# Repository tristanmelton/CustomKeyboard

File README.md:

### Custom Keyboard and Numpad - Beryl.
I had some problems with Amethyst, namely:
- USB-Micro instead of USB-C
- Wired takes up an already-limited USB slot
- A little tall to type on
- Non-customizable key switches

So for Beryl, I'm proposing:
- USB-C with the nice!nano microcontroller. Also covers wireless with the built-in bluetooth.
- Going to use Kailh switches with low-profile to shorten the height, with hot-swap sockets.  

### Changelog
## 1/25/2025
I did some initial re-organization and copied the v1 to a v2 folder for initial setup. The MCU was replaced with a nice!nano and I'm using hot-swappable Kailh choc switches now.
Board should be laid out and everything - it's been sent off with JLCPCB.

PURCHASED:
- PCB x5 from JLCPCB
- Battery from Amazon
- Kailh hot-swappable sockets x100 from AliExpress
- nice!nano v2 x5 from AliExpress
- JST Connector from Digikey
- Sliding switch from Digikey
- Kailh Low Profile Choc Switches (red) x80 from Typeractive

I only have not ordered Keycaps yet. If you have any suggestions please let me know.

## 2/11/2025
I have updated the PCB with a silly mistake that had GND and VCC swapped on the battery. The software is complete and can be found (https://github.com/tristanmelton/cheapino-zmk-config-single-nicenano). The direct uf2 is also in the Software folder.

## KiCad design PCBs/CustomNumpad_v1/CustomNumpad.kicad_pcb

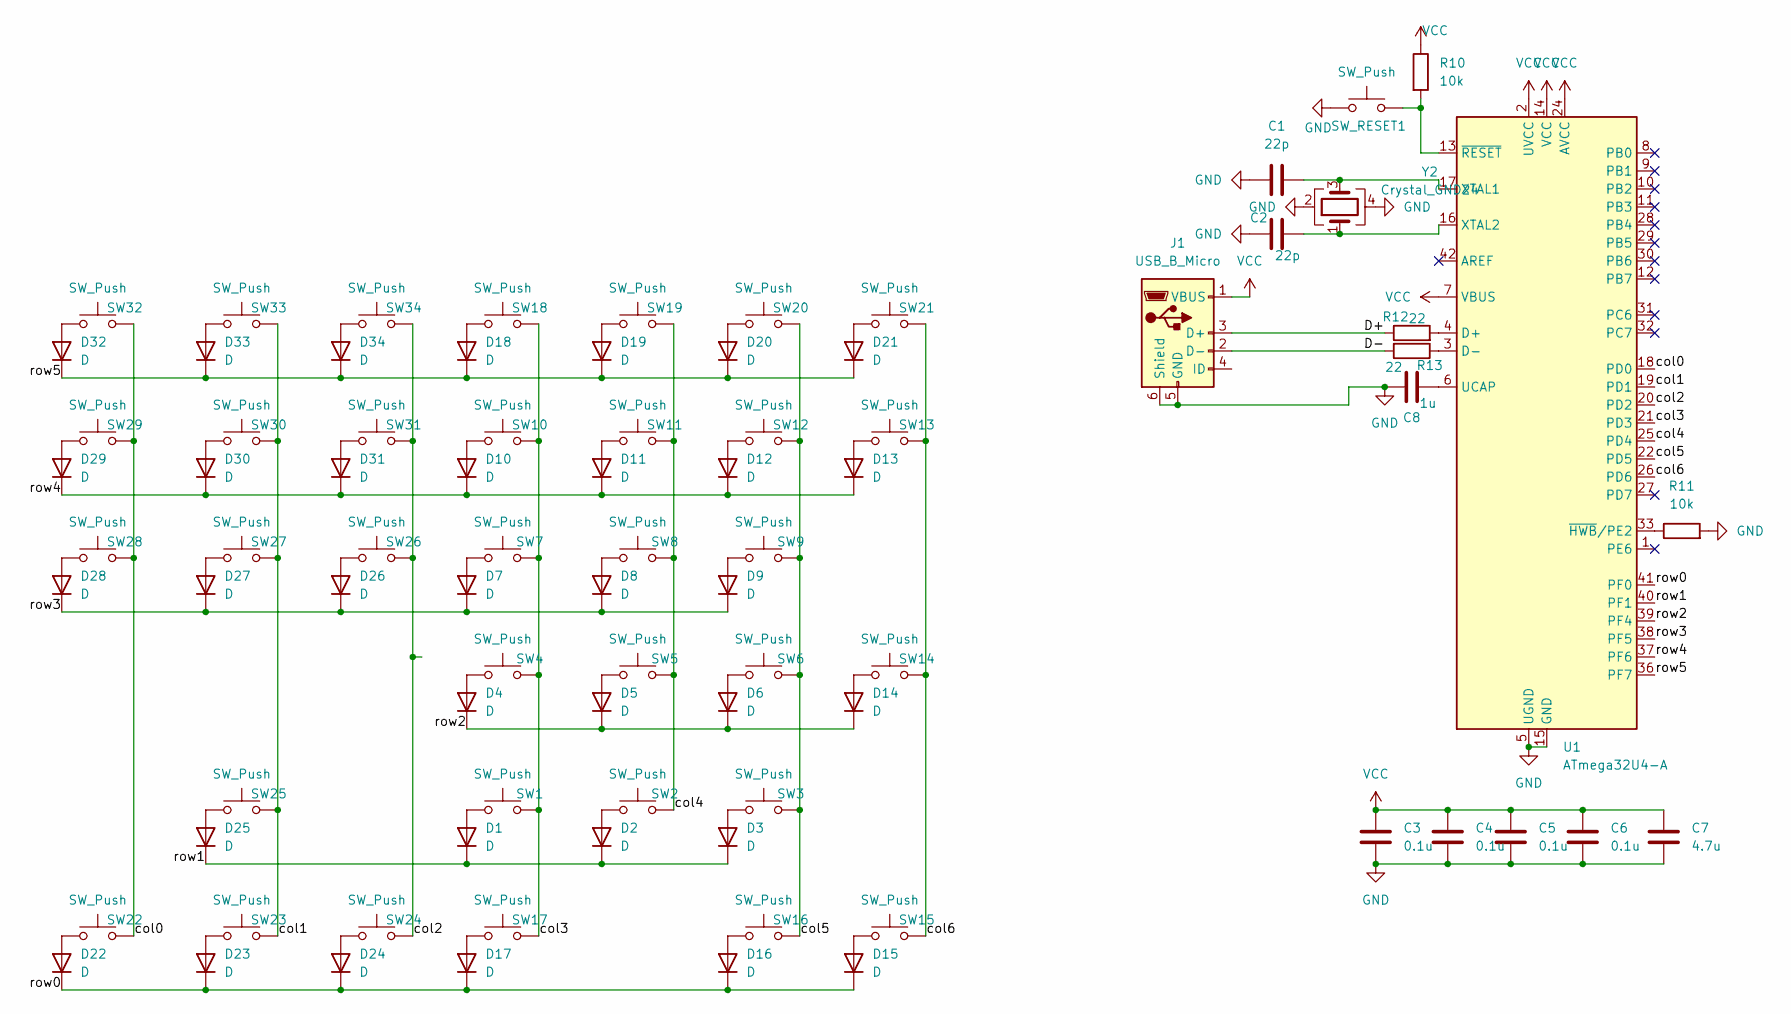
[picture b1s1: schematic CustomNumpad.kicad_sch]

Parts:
C1, C2: 22p; C_0603_1608Metric
C3, C4, C5, C6: 0.1u; C_0603_1608Metric
C7: 4.7u; C_0603_1608Metric
C8: 1u; C_0603_1608Metric
D1, D2, D3, D4, D5, D6, D7, D8, D9, D10, D11, D12, D13, D14, D15, D16, D17, D18, D19, D20, D21, D22, D23, D24, D25, D26, D27, D28, D29, D30, D31, D32, D33, D34: D; D_0603_1608Metric
J1: USB_B_Micro; USB_Micro-B_Amphenol_10118194_Horizontal
R10, R11: 10k; R_0603_1608Metric
R12, R13: 22; R_0603_1608Metric
SW1, SW2, SW3, SW4, SW5, SW6, SW7, SW8, SW9, SW10, SW11, SW12, SW13, SW16, SW18, SW19, SW20, SW21, SW22, SW23, SW24, SW25, SW26, SW27, SW28, SW29, SW30, SW31, SW32, SW33, SW34: SW_Push; SW_Cherry_MX_PCB_1.00u
SW14, SW15: SW_Push; SW_Cherry_MX_PCB_2.00u_90deg
SW17: SW_Push; SW_Cherry_MX_PCB_2.00u
SW_RESET1: SW_Push; SW_SPST_TL3342
U1: ATmega32U4-A; TQFP-44_10x10mm_P0.8mm
Y2: Crystal_GND24; Crystal_SMD_SeikoEpson_FA238-4Pin_3.2x2.5mm

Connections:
/D+: J1.3 (D+), R12.1
/D-: J1.2 (D-), R13.2
/col0: SW22.2, SW28.2, SW29.2, SW32.2, U1.18 (PD0)
/col1: SW23.2, SW25.2, SW27.2, SW30.2, SW33.2, U1.19 (PD1)
/col2: SW24.2, SW26.2, SW31.2, SW34.2, U1.20 (PD2)
/col3: SW1.2, SW4.2, SW7.2, SW10.2, SW17.2, SW18.2, U1.21 (PD3)
/col4: SW2.2, SW5.2, SW8.2, SW11.2, SW19.2, U1.25 (PD4)
/col5: SW3.2, SW6.2, SW9.2, SW12.2, SW16.2, SW20.2, U1.22 (PD5)
/col6: SW13.2, SW14.2, SW15.2, SW21.2, U1.26 (PD6)
/row0: D15.1 (K), D16.1 (K), D17.1 (K), D22.1 (K), D23.1 (K), D24.1 (K), U1.41 (PF0)
/row1: D1.1 (K), D2.1 (K), D3.1 (K), D25.1 (K), U1.40 (PF1)
/row2: D4.1 (K), D5.1 (K), D6.1 (K), D14.1 (K), U1.39 (PF4)
/row3: D7.1 (K), D8.1 (K), D9.1 (K), D26.1 (K), D27.1 (K), D28.1 (K), U1.38 (PF5)
/row4: D10.1 (K), D11.1 (K), D12.1 (K), D13.1 (K), D29.1 (K), D30.1 (K), D31.1 (K), U1.37 (PF6)
/row5: D18.1 (K), D19.1 (K), D20.1 (K), D21.1 (K), D32.1 (K), D33.1 (K), D34.1 (K), U1.36 (PF7)
GND: C1.1, C2.1, C3.2, C4.2, C5.2, C6.2, C7.2, C8.1, J1.5 (GND), J1.6 (Shield), R11.2, SW_RESET1.1, U1.5 (UGND), U1.15 (GND), U1.23 (GND), U1.35 (GND), U1.43 (GND), Y2.2, Y2.4
unnamed: D1.2 (A), SW1.1
unnamed: D2.2 (A), SW2.1
unnamed: D3.2 (A), SW3.1
unnamed: D4.2 (A), SW4.1
unnamed: D5.2 (A), SW5.1
unnamed: D6.2 (A), SW6.1
unnamed: D7.2 (A), SW7.1
unnamed: D8.2 (A), SW8.1
unnamed: D9.2 (A), SW9.1
unnamed: D10.2 (A), SW10.1
unnamed: D11.2 (A), SW11.1
unnamed: D12.2 (A), SW12.1
unnamed: D13.2 (A), SW13.1
unnamed: D14.2 (A), SW14.1
unnamed: D15.2 (A), SW15.1
unnamed: D16.2 (A), SW16.1
unnamed: D17.2 (A), SW17.1
unnamed: D18.2 (A), SW18.1
unnamed: D19.2 (A), SW19.1
unnamed: D20.2 (A), SW20.1
unnamed: D21.2 (A), SW21.1
unnamed: D22.2 (A), SW22.1
unnamed: D23.2 (A), SW23.1
unnamed: D24.2 (A), SW24.1
unnamed: D25.2 (A), SW25.1
unnamed: D26.2 (A), SW26.1
unnamed: D27.2 (A), SW27.1
unnamed: D28.2 (A), SW28.1
unnamed: D29.2 (A), SW29.1
unnamed: D30.2 (A), SW30.1
unnamed: D31.2 (A), SW31.1
unnamed: D32.2 (A), SW32.1
unnamed: D33.2 (A), SW33.1
unnamed: D34.2 (A), SW34.1
unnamed: R12.2, U1.4 (D+)
unnamed: R13.1, U1.3 (D-)
unnamed: C8.2, U1.6 (UCAP)
unnamed: C1.2, U1.17 (XTAL1), Y2.3
unnamed: C2.2, U1.16 (XTAL2), Y2.1
unnamed: R11.1, U1.33 (~HWB/PE2)
unnamed: R10.2, SW_RESET1.2, U1.13 (~RESET)
VCC: C3.1, C4.1, C5.1, C6.1, C7.1, J1.1 (VBUS), R10.1, U1.2 (UVCC), U1.7 (VBUS), U1.14 (VCC), U1.24 (AVCC), U1.34 (VCC), U1.44 (AVCC)

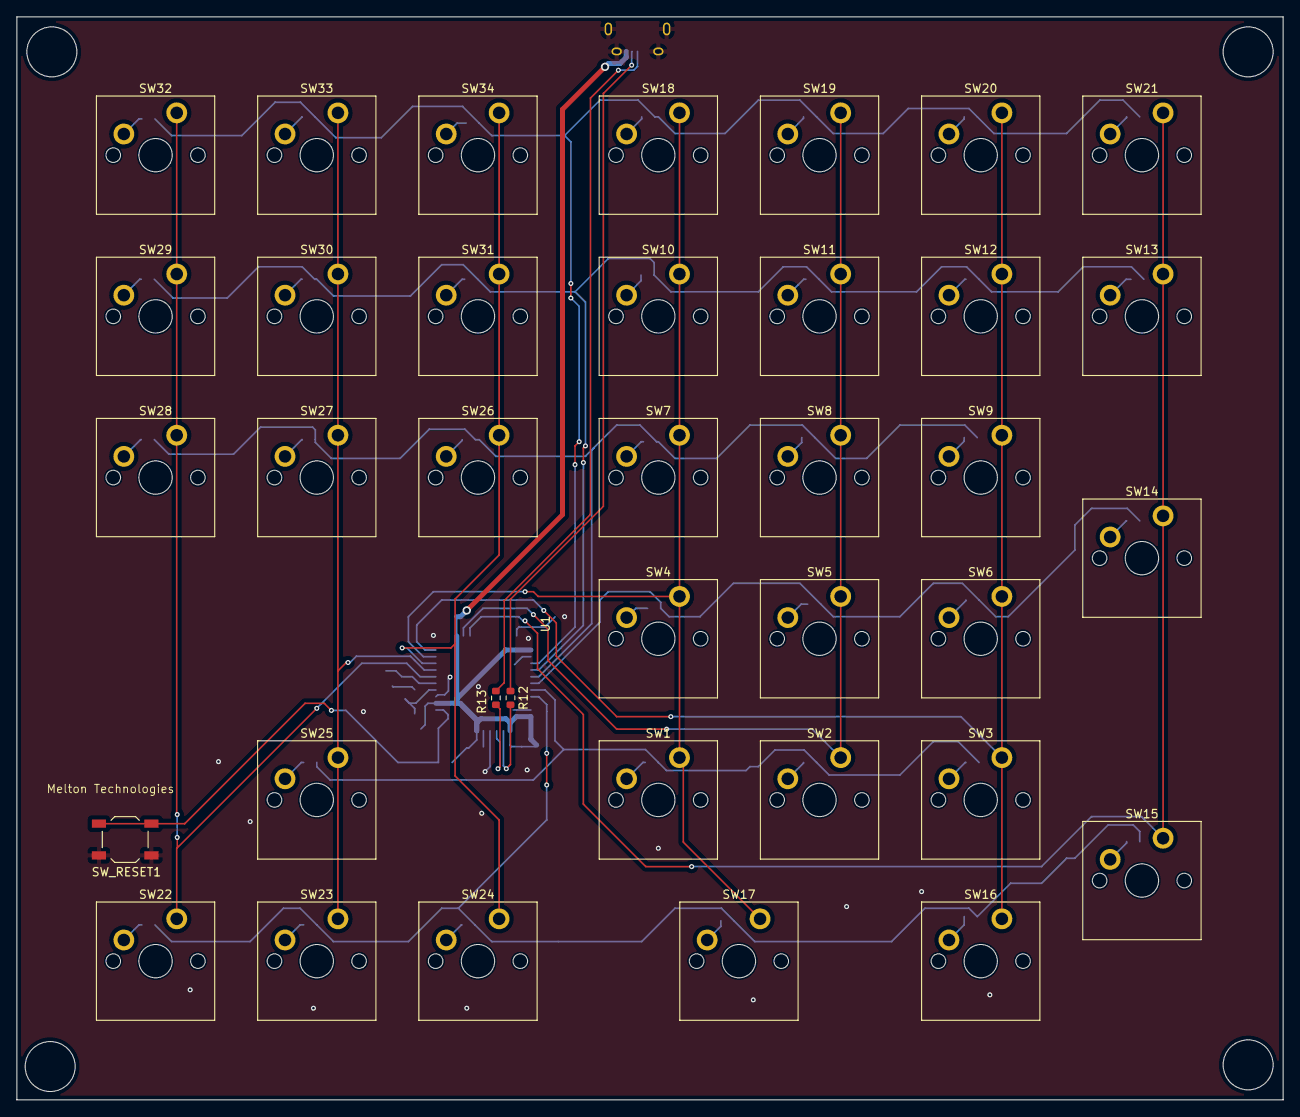
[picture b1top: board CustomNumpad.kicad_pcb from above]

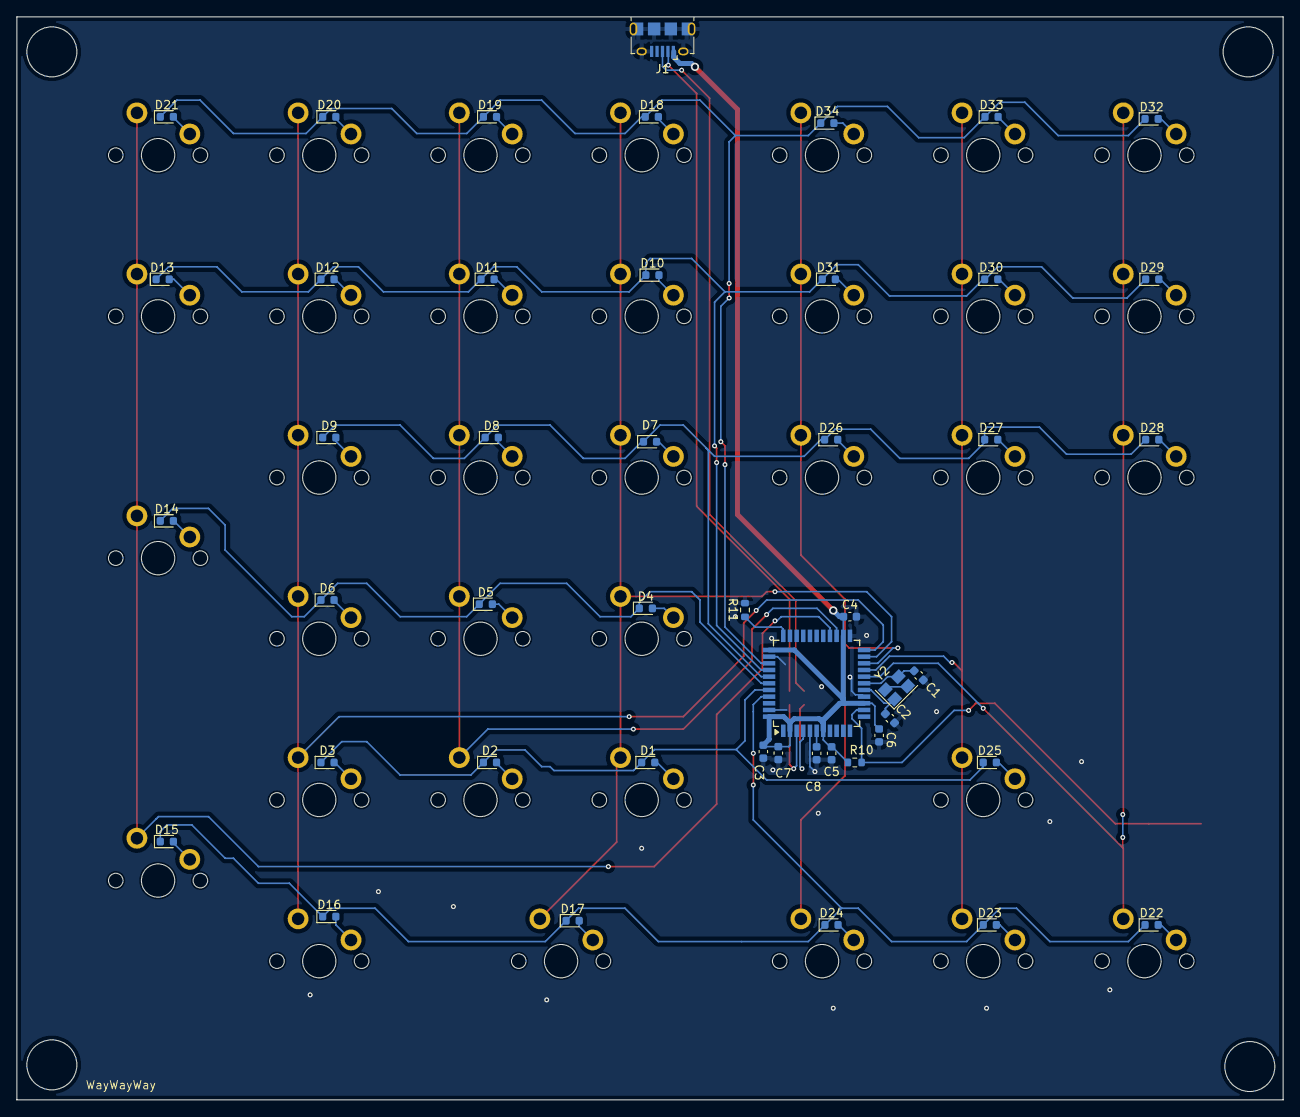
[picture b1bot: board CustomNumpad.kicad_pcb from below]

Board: 2 copper layers, 152.0 x 130.0 mm, 84 parts (47 on the bottom side), 58 nets.

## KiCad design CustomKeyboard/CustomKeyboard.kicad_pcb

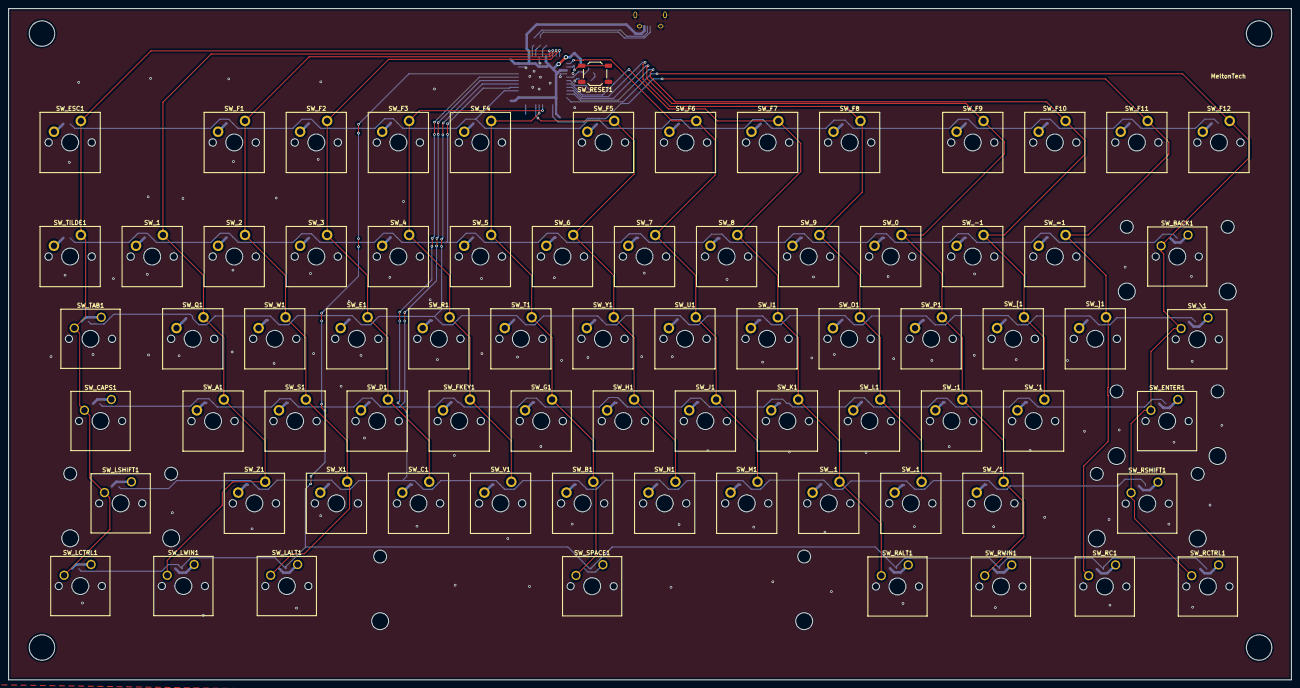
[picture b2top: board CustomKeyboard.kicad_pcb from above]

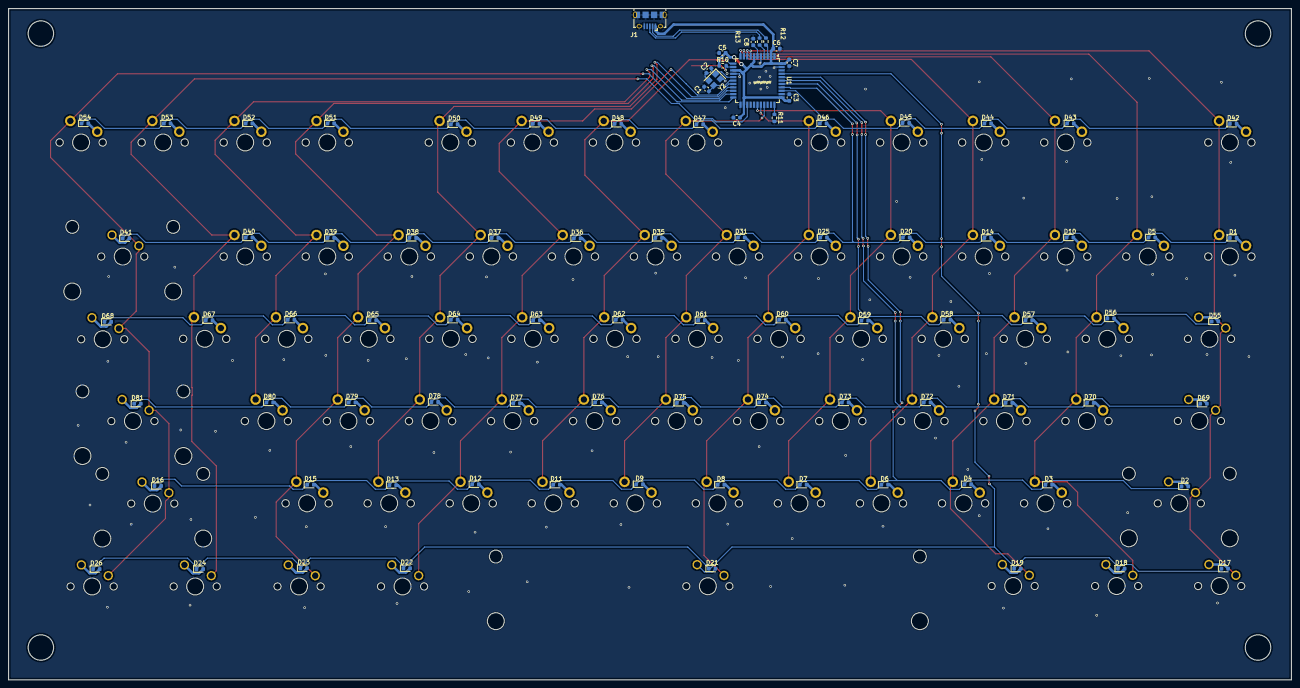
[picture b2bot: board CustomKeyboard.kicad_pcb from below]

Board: 2 copper layers, 302.5 x 158.3 mm, 164 parts (89 on the bottom side), 105 nets.

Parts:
C1, C2: 22p; C_0603_1608Metric
C3, C4, C5, C6: 0.1u; C_0603_1608Metric
C7: 4.7u; C_0603_1608Metric
C8: 1u; C_0603_1608Metric
D1, D2, D3, D4, D5, D6, D7, D8, D9, D10, D11, D12, D13, D14, D15, D16, D17, D18, D19, D20, D21, D22, D23, D24, D25, D26, D31, D35, D36, D37, D38, D39, D40, D41, D42, D43, D44, D45, D46, D47, D48, D49, D50, D51, D52, D53, D54, D55, D56, D57, D58, D59, D60, D61, D62, D63, D64, D65, D66, D67, D68, D69, D70, D71, D72, D73, D74, D75, D76, D77, D78, D79, D80, D81: D; D_0603_1608Metric
J1: USB_B_Micro; USB_Micro-B_Amphenol_10118194_Horizontal
R10, R11: 10k; R_0603_1608Metric
R12, R13: 22; R_0603_1608Metric
SW_0, SW_1, SW_2, SW_3, SW_4, SW_5, SW_6, SW_7, SW_8, SW_9, SW_.1: SW_Push; SW_Cherry_MX_PCB_1.00u
SW_'1: SW_Push; SW_Cherry_MX_PCB_1.00u
SW_,1: SW_Push; SW_Cherry_MX_PCB_1.00u
SW_-1: SW_Push; SW_Cherry_MX_PCB_1.00u
SW_/1: SW_Push; SW_Cherry_MX_PCB_1.00u
SW_;1: SW_Push; SW_Cherry_MX_PCB_1.00u
SW_=1: SW_Push; SW_Cherry_MX_PCB_1.00u
SW_A1: SW_Push; SW_Cherry_MX_PCB_1.00u
SW_B1: SW_Push; SW_Cherry_MX_PCB_1.00u
SW_BACK1: SW_Push; SW_Cherry_MX_2.00u_PCB
SW_C1: SW_Push; SW_Cherry_MX_PCB_1.00u
SW_CAPS1: SW_Push; SW_Cherry_MX_1.75u_PCB
SW_D1: SW_Push; SW_Cherry_MX_PCB_1.00u
SW_E1: SW_Push; SW_Cherry_MX_PCB_1.00u
SW_ENTER1: SW_Push; SW_Cherry_MX_2.25u_PCB
SW_ESC1: SW_Push; SW_Cherry_MX_PCB_1.00u
SW_F1, SW_F2, SW_F3, SW_F4, SW_F5, SW_F6, SW_F7, SW_F8, SW_F9, SW_F10, SW_F11, SW_F12: SW_Push; SW_Cherry_MX_PCB_1.00u
SW_FKEY1: SW_Push; SW_Cherry_MX_PCB_1.00u
SW_G1: SW_Push; SW_Cherry_MX_PCB_1.00u
SW_H1: SW_Push; SW_Cherry_MX_PCB_1.00u
SW_I1: SW_Push; SW_Cherry_MX_PCB_1.00u
SW_J1: SW_Push; SW_Cherry_MX_PCB_1.00u
SW_K1: SW_Push; SW_Cherry_MX_PCB_1.00u
SW_L1: SW_Push; SW_Cherry_MX_PCB_1.00u
SW_LALT1: SW_Push; SW_Cherry_MX_1.25u_PCB
SW_LCTRL1: SW_Push; SW_Cherry_MX_1.25u_PCB
SW_LSHIFT1: SW_Push; SW_Cherry_MX_2.25u_PCB
SW_LWIN1: SW_Push; SW_Cherry_MX_1.25u_PCB
SW_M1: SW_Push; SW_Cherry_MX_PCB_1.00u
SW_N1: SW_Push; SW_Cherry_MX_PCB_1.00u
SW_O1: SW_Push; SW_Cherry_MX_PCB_1.00u
SW_P1: SW_Push; SW_Cherry_MX_PCB_1.00u
SW_Q1: SW_Push; SW_Cherry_MX_PCB_1.00u
SW_R1: SW_Push; SW_Cherry_MX_PCB_1.00u
SW_RALT1: SW_Push; SW_Cherry_MX_1.25u_PCB
SW_RC1: SW_Push; SW_Cherry_MX_1.25u_PCB
SW_RCTRL1: SW_Push; SW_Cherry_MX_1.25u_PCB
SW_RESET1: SW_Push; SW_SPST_TL3342
SW_RSHIFT1: SW_Push; SW_Cherry_MX_2.75u_PCB
SW_RWIN1: SW_Push; SW_Cherry_MX_1.25u_PCB
SW_S1: SW_Push; SW_Cherry_MX_PCB_1.00u
SW_SPACE1: SW_Push; SW_Cherry_MX_6.25u_PCB
SW_T1: SW_Push; SW_Cherry_MX_PCB_1.00u
SW_TAB1: SW_Push; SW_Cherry_MX_1.50u_PCB
SW_TILDE1: SW_Push; SW_Cherry_MX_PCB_1.00u
SW_U1: SW_Push; SW_Cherry_MX_PCB_1.00u
SW_V1: SW_Push; SW_Cherry_MX_PCB_1.00u
SW_W1: SW_Push; SW_Cherry_MX_PCB_1.00u
SW_X1: SW_Push; SW_Cherry_MX_PCB_1.00u
SW_Y1: SW_Push; SW_Cherry_MX_PCB_1.00u
SW_Z1: SW_Push; SW_Cherry_MX_PCB_1.00u
SW_[1: SW_Push; SW_Cherry_MX_PCB_1.00u
SW_\1: SW_Push; SW_Cherry_MX_1.50u_PCB
SW_]1: SW_Push; SW_Cherry_MX_PCB_1.00u
U1: ATmega32U4-A; TQFP-44_10x10mm_P0.8mm
Y2: Crystal_GND24; Crystal_SMD_SeikoEpson_FA238-4Pin_3.2x2.5mm

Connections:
/D+: J1.3 (D+), R12.1
/D-: J1.2 (D-), R13.2
GND: C1.1, C2.1, C3.2, C4.2, C5.2, C6.2, C7.2, C8.1, J1.5 (GND), J1.6 (Shield), R11.2, SW_RESET1.1, U1.5 (UGND), U1.15 (GND), U1.23 (GND), U1.35 (GND), U1.43 (GND), Y2.2, Y2.4
unnamed: D1.2 (A), SW_TILDE1.1
unnamed: D2.2 (A), SW_LSHIFT1.1
unnamed: D3.2 (A), SW_Z1.1
unnamed: D4.2 (A), SW_X1.1
unnamed: D5.2 (A), SW_1.1
unnamed: D6.2 (A), SW_C1.1
unnamed: D7.2 (A), SW_V1.1
unnamed: D8.2 (A), SW_B1.1
unnamed: D9.2 (A), SW_N1.1
unnamed: D10.2 (A), SW_2.1
unnamed: D11.2 (A), SW_M1.1
unnamed: D12.2 (A), SW_,1.1
unnamed: D13.2 (A), SW_.1.1
unnamed: D14.2 (A), SW_3.1
unnamed: D15.2 (A), SW_/1.1
unnamed: D16.2 (A), SW_RSHIFT1.1
unnamed: D17.2 (A), SW_LCTRL1.1
unnamed: D18.2 (A), SW_LWIN1.1
unnamed: D19.2 (A), SW_LALT1.1
unnamed: D20.2 (A), SW_4.1
unnamed: D21.2 (A), SW_SPACE1.1
unnamed: D22.2 (A), SW_RALT1.1
unnamed: D23.2 (A), SW_RWIN1.1
unnamed: D24.2 (A), SW_RC1.1
unnamed: D25.2 (A), SW_5.1
unnamed: D26.2 (A), SW_RCTRL1.1
unnamed: D31.2 (A), SW_6.1
unnamed: D35.2 (A), SW_7.1
unnamed: D36.2 (A), SW_8.1
unnamed: D37.2 (A), SW_9.1
unnamed: D38.2 (A), SW_0.1
unnamed: D39.2 (A), SW_-1.1
unnamed: D40.2 (A), SW_=1.1
unnamed: D41.2 (A), SW_BACK1.1
unnamed: D42.2 (A), SW_ESC1.1
unnamed: D43.2 (A), SW_F1.1
unnamed: D44.2 (A), SW_F2.1
unnamed: D45.2 (A), SW_F3.1
unnamed: D46.2 (A), SW_F4.1
unnamed: D47.2 (A), SW_F5.1
unnamed: D48.2 (A), SW_F6.1
unnamed: D49.2 (A), SW_F7.1
unnamed: D50.2 (A), SW_F8.1
unnamed: D51.2 (A), SW_F9.1
unnamed: D52.2 (A), SW_F10.1
unnamed: D53.2 (A), SW_F11.1
unnamed: D54.2 (A), SW_F12.1
unnamed: D55.2 (A), SW_TAB1.1
unnamed: D56.2 (A), SW_Q1.1
unnamed: D57.2 (A), SW_W1.1
unnamed: D58.2 (A), SW_E1.1
unnamed: D59.2 (A), SW_R1.1
unnamed: D60.2 (A), SW_T1.1
unnamed: D61.2 (A), SW_Y1.1
unnamed: D62.2 (A), SW_U1.1
unnamed: D63.2 (A), SW_I1.1
unnamed: D64.2 (A), SW_O1.1
unnamed: D65.2 (A), SW_P1.1
unnamed: D66.2 (A), SW_[1.1
unnamed: D67.2 (A), SW_]1.1
unnamed: D68.2 (A), SW_\1.1
unnamed: D69.2 (A), SW_CAPS1.1
unnamed: D70.2 (A), SW_A1.1
unnamed: D71.2 (A), SW_S1.1
unnamed: D72.2 (A), SW_D1.1
unnamed: D73.2 (A), SW_FKEY1.1
unnamed: D74.2 (A), SW_G1.1
unnamed: D75.2 (A), SW_H1.1
unnamed: D76.2 (A), SW_J1.1
unnamed: D77.2 (A), SW_K1.1
unnamed: D78.2 (A), SW_L1.1
unnamed: D79.2 (A), SW_;1.1
unnamed: D80.2 (A), SW_'1.1
unnamed: D81.2 (A), SW_ENTER1.1
unnamed: R12.2, U1.4 (D+)
unnamed: R13.1, U1.3 (D-)
unnamed: C8.2, U1.6 (UCAP)
unnamed: C1.2, U1.17 (XTAL1), Y2.3
unnamed: C2.2, U1.16 (XTAL2), Y2.1
unnamed: R11.1, U1.33 (~HWB/PE2)
unnamed: R10.2, SW_RESET1.2, U1.13 (~RESET)
VCC: C3.1, C4.1, C5.1, C6.1, C7.1, J1.1 (VBUS), R10.1, U1.2 (UVCC), U1.7 (VBUS), U1.14 (VCC), U1.24 (AVCC), U1.34 (VCC), U1.44 (AVCC)
col0: SW_CAPS1.2, SW_ESC1.2, SW_LCTRL1.2, SW_LSHIFT1.2, SW_TAB1.2, SW_TILDE1.2, U1.8 (PB0)
col1: SW_1.2, SW_A1.2, SW_LWIN1.2, SW_Q1.2, SW_Z1.2, U1.9 (PB1)
col2: SW_2.2, SW_F1.2, SW_LALT1.2, SW_S1.2, SW_W1.2, SW_X1.2, U1.10 (PB2)
col3: SW_3.2, SW_C1.2, SW_D1.2, SW_E1.2, SW_F2.2, U1.11 (PB3)
col4: SW_4.2, SW_F3.2, SW_FKEY1.2, SW_R1.2, SW_V1.2, U1.28 (PB4)
col5: SW_5.2, SW_B1.2, SW_F4.2, SW_G1.2, SW_SPACE1.2, SW_T1.2, U1.29 (PB5)
col6: SW_6.2, SW_F5.2, SW_H1.2, SW_N1.2, SW_Y1.2, U1.30 (PB6)
col7: SW_7.2, SW_F6.2, SW_J1.2, SW_M1.2, SW_U1.2, U1.12 (PB7)
col8: SW_8.2, SW_,1.2, SW_F7.2, SW_I1.2, SW_K1.2, SW_RALT1.2, U1.18 (PD0)
col9: SW_9.2, SW_.1.2, SW_F8.2, SW_L1.2, SW_O1.2, U1.19 (PD1)
col10: SW_0.2, SW_/1.2, SW_;1.2, SW_F9.2, SW_P1.2, SW_RWIN1.2, U1.20 (PD2)
col11: SW_'1.2, SW_-1.2, SW_F10.2, SW_[1.2, U1.21 (PD3)
col12: SW_=1.2, SW_F11.2, SW_RC1.2, SW_]1.2, U1.25 (PD4)
col13: SW_BACK1.2, SW_ENTER1.2, SW_F12.2, SW_RCTRL1.2, SW_RSHIFT1.2, SW_\1.2, U1.22 (PD5)
row0: D17.1 (K), D18.1 (K), D19.1 (K), D21.1 (K), D22.1 (K), D23.1 (K), D24.1 (K), D26.1 (K), U1.41 (PF0)
row1: D2.1 (K), D3.1 (K), D4.1 (K), D6.1 (K), D7.1 (K), D8.1 (K), D9.1 (K), D11.1 (K), D12.1 (K), D13.1 (K), D15.1 (K), D16.1 (K), U1.40 (PF1)
row2: D69.1 (K), D70.1 (K), D71.1 (K), D72.1 (K), D73.1 (K), D74.1 (K), D75.1 (K), D76.1 (K), D77.1 (K), D78.1 (K), D79.1 (K), D80.1 (K), D81.1 (K), U1.39 (PF4)
row3: D55.1 (K), D56.1 (K), D57.1 (K), D58.1 (K), D59.1 (K), D60.1 (K), D61.1 (K), D62.1 (K), D63.1 (K), D64.1 (K), D65.1 (K), D66.1 (K), D67.1 (K), D68.1 (K), U1.38 (PF5)
row4: D1.1 (K), D5.1 (K), D10.1 (K), D14.1 (K), D20.1 (K), D25.1 (K), D31.1 (K), D35.1 (K), D36.1 (K), D37.1 (K), D38.1 (K), D39.1 (K), D40.1 (K), D41.1 (K), U1.37 (PF6)
row5: D42.1 (K), D43.1 (K), D44.1 (K), D45.1 (K), D46.1 (K), D47.1 (K), D48.1 (K), D49.1 (K), D50.1 (K), D51.1 (K), D52.1 (K), D53.1 (K), D54.1 (K), U1.36 (PF7)

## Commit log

2024-08-17 Initial Commit. Will add the 3D model for the case later.
2025-01-26 Beginning work on Keyboard-Beryl.
2025-01-26 Finalized purchases. Still need to order keycaps....
2025-02-12 Completed Build!
